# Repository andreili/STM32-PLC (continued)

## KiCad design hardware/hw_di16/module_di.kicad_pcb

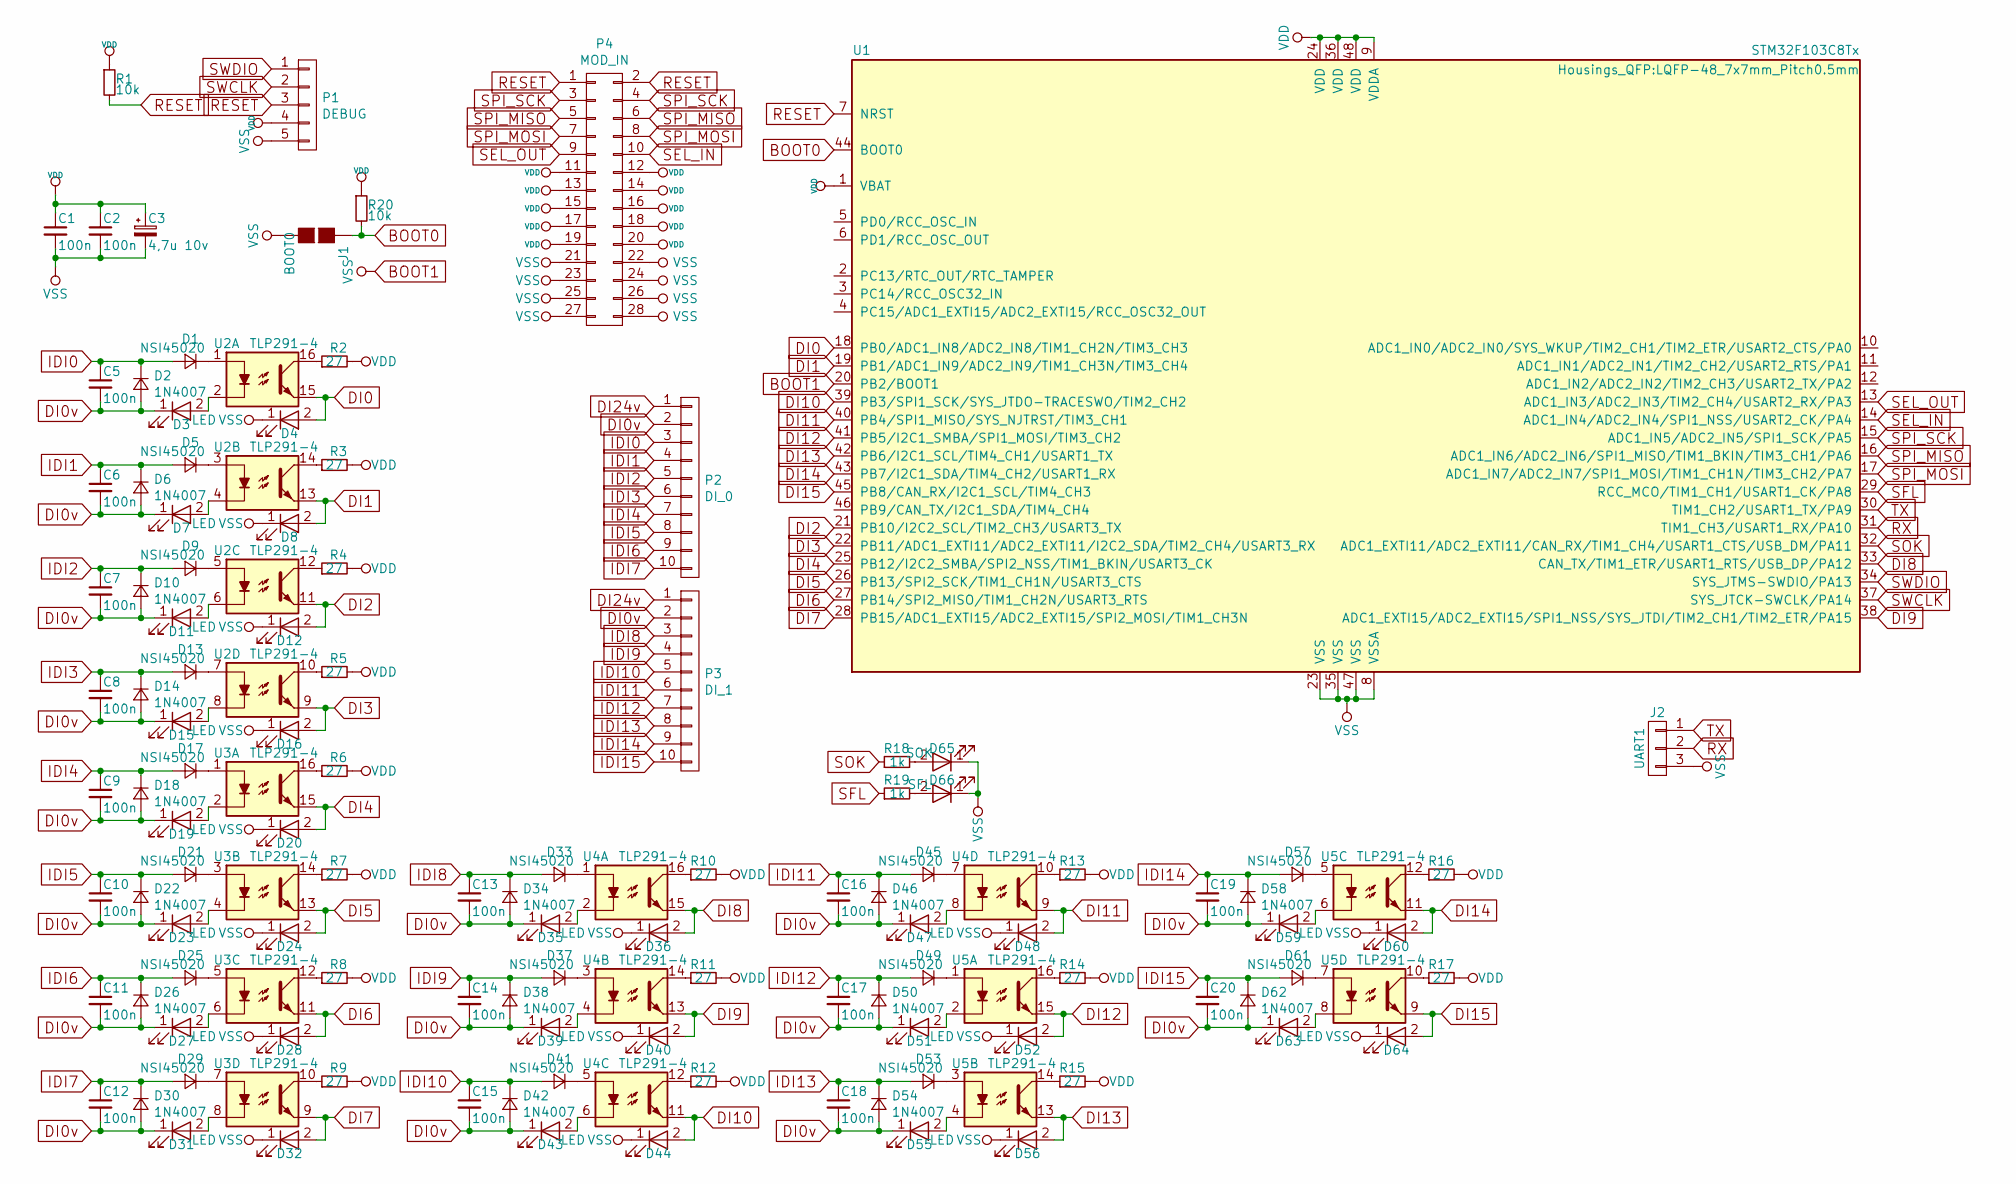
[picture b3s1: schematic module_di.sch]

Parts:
C1, C2, C5, C6, C7, C8, C9, C10, C11, C12, C13, C14, C15, C16, C17, C18, C19, C20: 100n; C_0805
C3: 4,7u 10v; CP_Tantalum_Case-A_EIA-3216-18_Reflow
D1, D5, D9, D13, D17, D21, D25, D29, D33, D37, D41, D45, D49, D53, D57, D61: NSI45020; D_SOD-123
D2, D6, D10, D14, D18, D22, D26, D30, D34, D38, D42, D46, D50, D54, D58, D62: 1N4007; D_SOD-123
D3, D4, D7, D8, D11, D12, D15, D16, D19, D20, D23, D24, D27, D28, D31, D32, D35, D36, D39, D40, D43, D44, D47, D48, D51, D52, D55, D56, D59, D60, D63, D64: LED; LED_0603
D65: SOK; LED_0603
D66: SFL; LED_0603
J1: BOOT0; GS2
J2: UART1; Pin_Header_Straight_1x03_Pitch2.00mm
P1: DEBUG; Pin_Header_Straight_1x05_Pitch2.00mm
P2: DI_0; PhoenixContact_MC-G_10x3.81mm_Angled
P3: DI_1; PhoenixContact_MC-G_10x3.81mm_Angled
P4: MOD_IN; Pin_Header_2.00mm_SMD
R1, R20: 10k; R_0805
R2, R3, R4, R5, R6, R7, R8, R9, R10, R11, R12, R13, R14, R15, R16, R17: 27; R_0805
R18, R19: 1k; R_0805
U1: STM32F103C8Tx; LQFP-48_7x7mm_Pitch0.5mm
U2, U3, U4, U5: TLP291-4; SO-16-N

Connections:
BOOT0: J1.1 (G1), R20.2, U1.44 (BOOT0)
BOOT1: C1.2, C2.2, C3.2, D4.1 (K), D8.1 (K), D12.1 (K), D16.1 (K), D20.1 (K), D24.1 (K), D28.1 (K), D32.1 (K), D36.1 (K), D40.1 (K), D44.1 (K), D48.1 (K), D52.1 (K), D56.1 (K), D60.1 (K), D64.1 (K), D65.1 (K), D66.1 (K), J1.2 (G2), J2.3, P1.5, P4.21, P4.22, P4.23, P4.24, P4.25, P4.26, P4.27, P4.28, U1.8 (VSSA), U1.20 (PB2/BOOT1), U1.23 (VSS), U1.35 (VSS), U1.47 (VSS)
DI0: D4.2 (A), U1.18 (PB0/ADC1_IN8/ADC2_IN8/TIM1_CH2N/TIM3_CH3), U2.15
DI0v: C5.2, C6.2, C7.2, C8.2, C9.2, C10.2, C11.2, C12.2, C13.2, C14.2, C15.2, C16.2, C17.2, C18.2, C19.2, C20.2, D2.2 (A), D3.1 (K), D6.2 (A), D7.1 (K), D10.2 (A), D11.1 (K), D14.2 (A), D15.1 (K), D18.2 (A), D19.1 (K), D22.2 (A), D23.1 (K), D26.2 (A), D27.1 (K), D30.2 (A), D31.1 (K), D34.2 (A), D35.1 (K), D38.2 (A), D39.1 (K), D42.2 (A), D43.1 (K), D46.2 (A), D47.1 (K), D50.2 (A), D51.1 (K), D54.2 (A), D55.1 (K), D58.2 (A), D59.1 (K), D62.2 (A), D63.1 (K), P2.2, P3.2
DI1: D8.2 (A), U1.19 (PB1/ADC1_IN9/ADC2_IN9/TIM1_CH3N/TIM3_CH4), U2.13
DI2: D12.2 (A), U1.21 (PB10/I2C2_SCL/TIM2_CH3/USART3_TX), U2.11
DI3: D16.2 (A), U1.22 (PB11/ADC1_EXTI11/ADC2_EXTI11/I2C2_SDA/T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), U2.9
DI4: D20.2 (A), U1.25 (PB12/I2C2_SMBA/SPI2_NSS/TIM1_BKIN/USART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), U3.15
DI5: D24.2 (A), U1.26 (PB13/SPI2_SCK/TIM1_CH1N/USART3_CTS), U3.13
DI6: D28.2 (A), U1.27 (PB14/SPI2_MISO/TIM1_CH2N/USART3_RTS), U3.11
DI7: D32.2 (A), U1.28 (PB15/ADC1_EXTI15/ADC2_EXTI15/SPI2_MOSI/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), U3.9
DI8: D36.2 (A), U1.33 (CAN_TX/TIM1_ETR/USART1_RTS/USB_DP/PA12), U4.15
DI9: D40.2 (A), U1.38 (ADC1_EXTI15/ADC2_EXTI15/SPI1_NSS/SYS_JT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), U4.13
DI10: D44.2 (A), U1.39 (PB3/SPI1_SCK/SYS_JTDO-TRACESWO/TIM2_CH2), U4.11
DI11: D48.2 (A), U1.40 (PB4/SPI1_MISO/SYS_NJTRST/TIM3_CH1), U4.9
DI12: D52.2 (A), U1.41 (PB5/I2C1_SMBA/SPI1_MOSI/TIM3_CH2), U5.15
DI13: D56.2 (A), U1.42 (PB6/I2C1_SCL/TIM4_CH1/USART1_TX), U5.13
DI14: D60.2 (A), U1.43 (PB7/I2C1_SDA/TIM4_CH2/USART1_RX), U5.11
DI15: D64.2 (A), U1.45 (PB8/CAN_RX/I2C1_SCL/TIM4_CH3), U5.9
DI24v: P2.1, P3.1
IDI0: C5.1, D1.2 (A), D2.1 (K), P2.3
IDI1: C6.1, D5.2 (A), D6.1 (K), P2.4
IDI2: C7.1, D9.2 (A), D10.1 (K), P2.5
IDI3: C8.1, D13.2 (A), D14.1 (K), P2.6
IDI4: C9.1, D17.2 (A), D18.1 (K), P2.7
IDI5: C10.1, D21.2 (A), D22.1 (K), P2.8
IDI6: C11.1, D25.2 (A), D26.1 (K), P2.9
IDI7: C12.1, D29.2 (A), D30.1 (K), P2.10
IDI8: C13.1, D33.2 (A), D34.1 (K), P3.3
IDI9: C14.1, D37.2 (A), D38.1 (K), P3.4
IDI10: C15.1, D41.2 (A), D42.1 (K), P3.5
IDI11: C16.1, D45.2 (A), D46.1 (K), P3.6
IDI12: C17.1, D49.2 (A), D50.1 (K), P3.7
IDI13: C18.1, D53.2 (A), D54.1 (K), P3.8
IDI14: C19.1, D57.2 (A), D58.1 (K), P3.9
IDI15: C20.1, D61.2 (A), D62.1 (K), P3.10
unnamed: D1.1 (K), U2.1
unnamed: D3.2 (A), U2.2
unnamed: D5.1 (K), U2.3
unnamed: D7.2 (A), U2.4
unnamed: D9.1 (K), U2.5
unnamed: D11.2 (A), U2.6
unnamed: D13.1 (K), U2.7
unnamed: D15.2 (A), U2.8
unnamed: D17.1 (K), U3.1
unnamed: D19.2 (A), U3.2
unnamed: D21.1 (K), U3.3
unnamed: D23.2 (A), U3.4
unnamed: D25.1 (K), U3.5
unnamed: D27.2 (A), U3.6
unnamed: D29.1 (K), U3.7
unnamed: D31.2 (A), U3.8
unnamed: D33.1 (K), U4.1
unnamed: D35.2 (A), U4.2
unnamed: D37.1 (K), U4.3
unnamed: D39.2 (A), U4.4
unnamed: D41.1 (K), U4.5
unnamed: D43.2 (A), U4.6
unnamed: D45.1 (K), U4.7
unnamed: D47.2 (A), U4.8
unnamed: D49.1 (K), U5.1
unnamed: D51.2 (A), U5.2
unnamed: D53.1 (K), U5.3
unnamed: D55.2 (A), U5.4
unnamed: D57.1 (K), U5.5
unnamed: D59.2 (A), U5.6
unnamed: D61.1 (K), U5.7
unnamed: D63.2 (A), U5.8
unnamed: D65.2 (A), R18.2
unnamed: D66.2 (A), R19.2
unnamed: R2.1, U2.16
unnamed: R3.1, U2.14
unnamed: R4.1, U2.12
unnamed: R5.1, U2.10
unnamed: R6.1, U3.16
unnamed: R7.1, U3.14
unnamed: R8.1, U3.12
unnamed: R9.1, U3.10
unnamed: R10.1, U4.16
unnamed: R11.1, U4.14
unnamed: R12.1, U4.12
unnamed: R13.1, U4.10
unnamed: R14.1, U5.16
unnamed: R15.1, U5.14
unnamed: R16.1, U5.12
unnamed: R17.1, U5.10
RESET: P1.3, P4.1, P4.2, R1.2, U1.7 (NRST)
RX: J2.2, U1.31 (TIM1_CH3/USART1_RX/PA10)
SEL_IN: P4.10, U1.14 (ADC1_IN4/ADC2_IN4/SPI1_NSS/USART2_CK/PA4)
SEL_OUT: P4.9, U1.13 (ADC1_IN3/ADC2_IN3/TIM2_CH4/USART2_RX/PA3)
SFL: R19.1, U1.29 (RCC_MCO/TIM1_CH1/USART1_CK/PA8)
SOK: R18.1, U1.32 (ADC1_EXTI11/ADC2_EXTI11/CAN_RX/TIM1_CH4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)
SPI_MISO: P4.5, P4.6, U1.16 (ADC1_IN6/ADC2_IN6/SPI1_MISO/TIM1_BKIN/T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)
SPI_MOSI: P4.7, P4.8, U1.17 (ADC1_IN7/ADC2_IN7/SPI1_MOSI/TIM1_CH1N/T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)
SPI_SCK: P4.3, P4.4, U1.15 (ADC1_IN5/ADC2_IN5/SPI1_SCK/PA5)
SWCLK: P1.2, U1.37 (SYS_JTCK-SWCLK/PA14)
SWDIO: P1.1, U1.34 (SYS_JTMS-SWDIO/PA13)
TX: J2.1, U1.30 (TIM1_CH2/USART1_TX/PA9)
VDD: C1.1, C2.1, C3.1, P1.4, P4.11, P4.12, P4.13, P4.14, P4.15, P4.16, P4.17, P4.18, P4.19, P4.20, R1.1, R2.2, R3.2, R4.2, R5.2, R6.2, R7.2, R8.2, R9.2, R10.2, R11.2, R12.2, R13.2, R14.2, R15.2, R16.2, R17.2, R20.1, U1.1 (VBAT), U1.9 (VDDA), U1.24 (VDD), U1.36 (VDD), U1.48 (VDD)

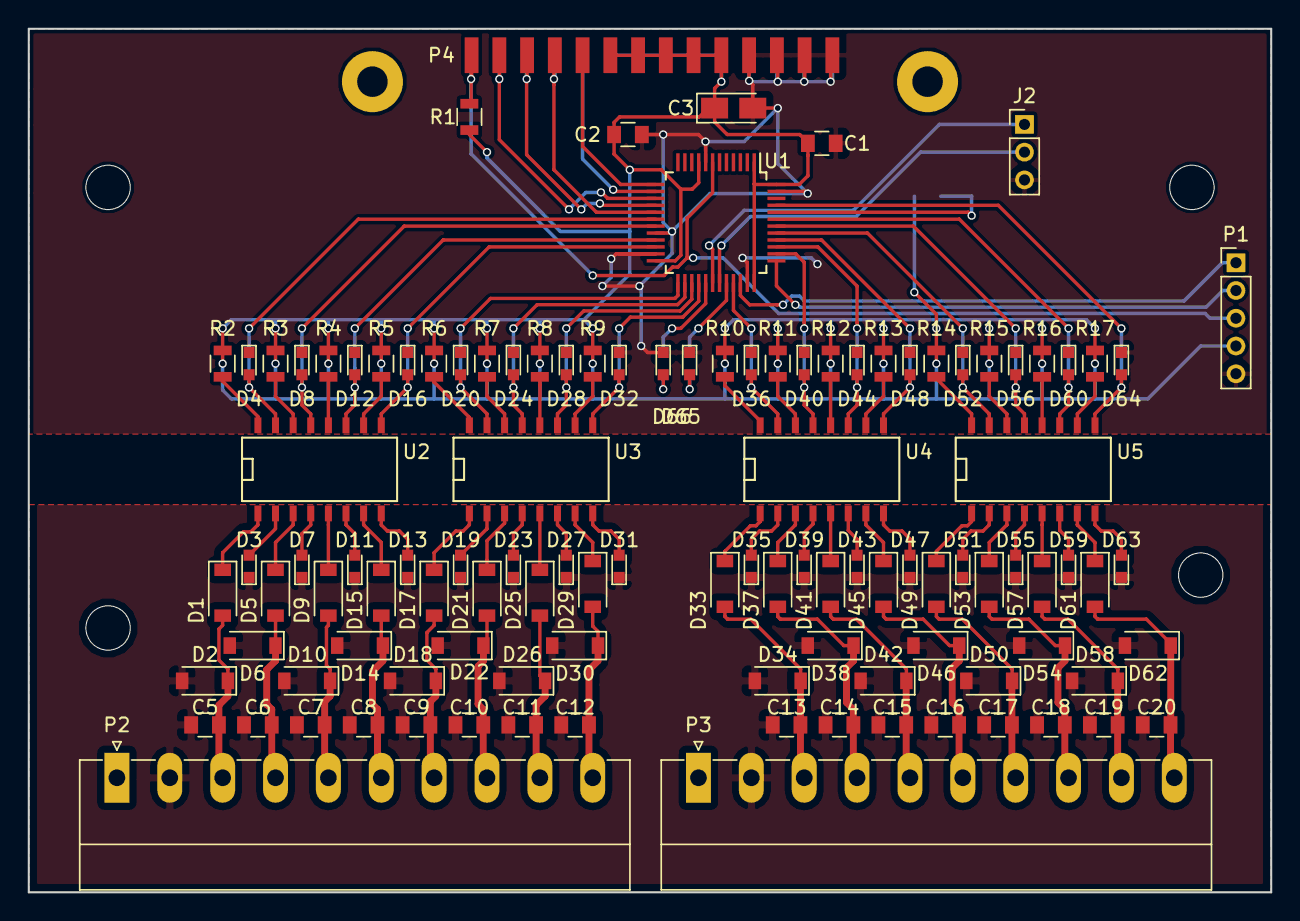
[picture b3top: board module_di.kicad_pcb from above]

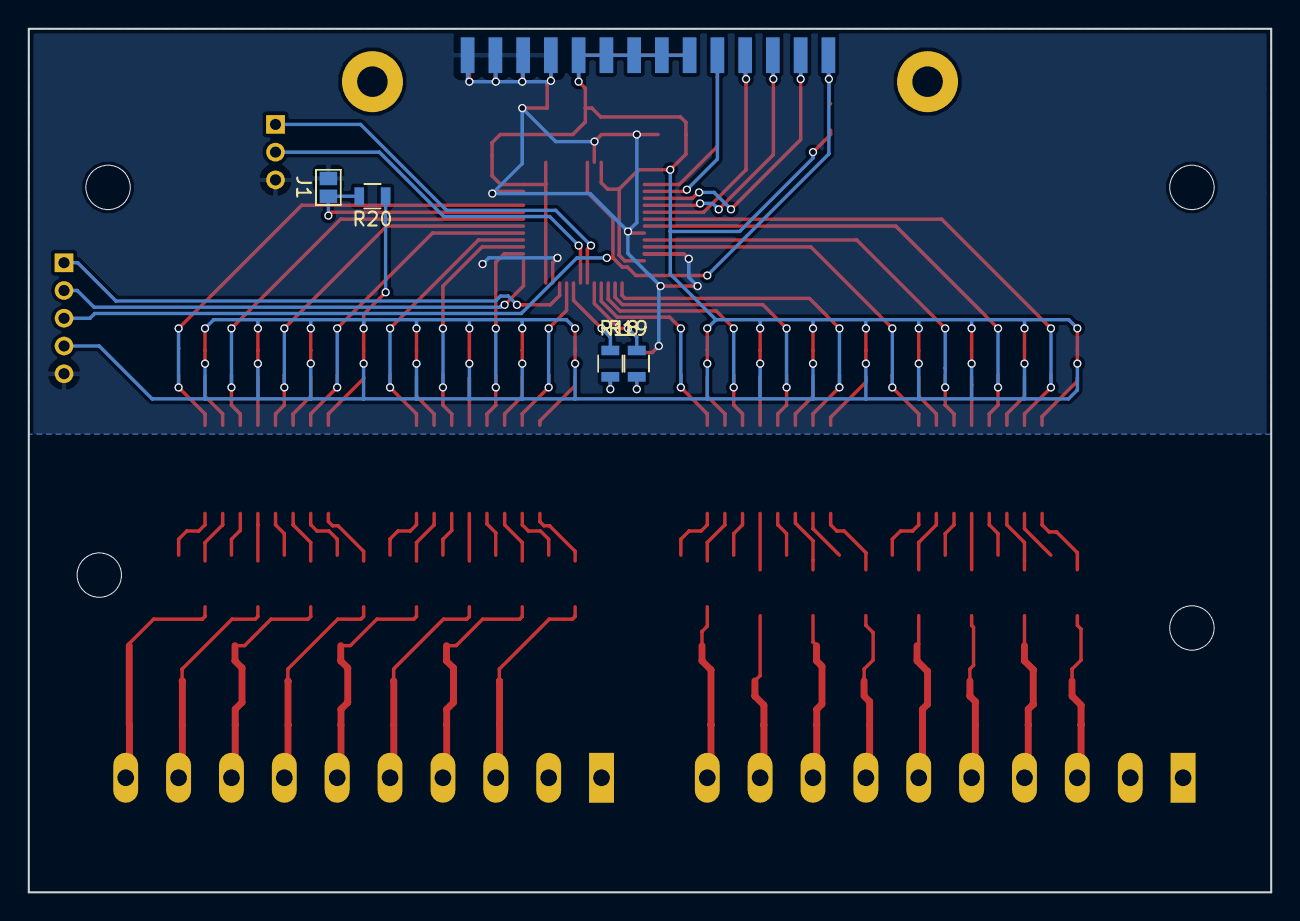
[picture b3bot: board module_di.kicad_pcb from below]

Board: 2 copper layers, 89.5 x 62.2 mm, 116 parts (4 on the bottom side), 99 nets.

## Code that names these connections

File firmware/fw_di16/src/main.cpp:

/* Includes ------------------------------------------------------------------*/
extern "C" {
#include "main.h"
#include "stm32f1xx_hal.h"
}

/* USER CODE BEGIN Includes */
#include "plc_mod.h"
/* USER CODE END Includes */

/* Private variables ---------------------------------------------------------*/
IWDG_HandleTypeDef hiwdg;

SPI_HandleTypeDef hspi1;
DMA_HandleTypeDef hdma_spi1_rx;
DMA_HandleTypeDef hdma_spi1_tx;

/* USER CODE BEGIN PV */
/* Private variables ---------------------------------------------------------*/

/* USER CODE END PV */

/* Private function prototypes -----------------------------------------------*/
void SystemClock_Config(void);
static void MX_GPIO_Init(void);
static void MX_DMA_Init(void);
static void MX_SPI1_Init(void);
static void MX_IWDG_Init(void);

/* USER CODE BEGIN PFP */
/* Private function prototypes -----------------------------------------------*/

/* USER CODE END PFP */

/* USER CODE BEGIN 0 */

/* USER CODE END 0 */

extern "C" {
int main(void)
{

  /* USER CODE BEGIN 1 */

  /* USER CODE END 1 */

  /* MCU Configuration----------------------------------------------------------*/

  /* Reset of all peripherals, Initializes the Flash interface and the Systick. */
  HAL_Init();

  /* USER CODE BEGIN Init */

  /* USER CODE END Init */

  /* Configure the system clock */
  SystemClock_Config();

  /* USER CODE BEGIN SysInit */

  /* USER CODE END SysInit */

  /* Initialize all configured peripherals */
  MX_GPIO_Init();
  MX_DMA_Init();
  MX_SPI1_Init();
  //MX_IWDG_Init();

  /* USER CODE BEGIN 2 */
  HAL_GPIO_WritePin(SEL_IN_GPIO_Port, SEL_IN_Pin, GPIO_PIN_SET);
  //HAL_Delay(300);
  plc_mod.init(&hspi1);
  plc_mod.init_seq();
  /* USER CODE END 2 */

  /* Infinite loop */
  /* USER CODE BEGIN WHILE */
  while (1)
  {
  /* USER CODE END WHILE */

  /* USER CODE BEGIN 3 */

  }
  /* USER CODE END 3 */

}
}

/** System Clock Configuration
*/
void SystemClock_Config(void)
{

  RCC_OscInitTypeDef RCC_OscInitStruct;
  RCC_ClkInitTypeDef RCC_ClkInitStruct;

    /**Initializes the CPU, AHB and APB busses clocks 
    */
  RCC_OscInitStruct.OscillatorType = RCC_OSCILLATORTYPE_HSI|RCC_OSCILLATORTYPE_LSI;
  RCC_OscInitStruct.HSIState = RCC_HSI_ON;
  RCC_OscInitStruct.HSICalibrationValue = 16;
  RCC_OscInitStruct.LSIState = RCC_LSI_ON;
  RCC_OscInitStruct.PLL.PLLState = RCC_PLL_ON;
  RCC_OscInitStruct.PLL.PLLSource = RCC_PLLSOURCE_HSI_DIV2;
  RCC_OscInitStruct.PLL.PLLMUL = RCC_PLL_MUL16;
  if (HAL_RCC_OscConfig(&RCC_OscInitStruct) != HAL_OK)
  {
    Error_Handler();
  }

    /**Initializes the CPU, AHB and APB busses clocks 
    */
  RCC_ClkInitStruct.ClockType = RCC_CLOCKTYPE_HCLK|RCC_CLOCKTYPE_SYSCLK
                              |RCC_CLOCKTYPE_PCLK1|RCC_CLOCKTYPE_PCLK2;
  RCC_ClkInitStruct.SYSCLKSource = RCC_SYSCLKSOURCE_PLLCLK;
  RCC_ClkInitStruct.AHBCLKDivider = RCC_SYSCLK_DIV1;
  RCC_ClkInitStruct.APB1CLKDivider = RCC_HCLK_DIV2;
  RCC_ClkInitStruct.APB2CLKDivider = RCC_HCLK_DIV1;

  if (HAL_RCC_ClockConfig(&RCC_ClkInitStruct, FLASH_LATENCY_2) != HAL_OK)
  {
    Error_Handler();
  }

    /**Configure the Systick interrupt time 
    */
  HAL_SYSTICK_Config(HAL_RCC_GetHCLKFreq()/1000);

    /**Configure the Systick 
    */
  HAL_SYSTICK_CLKSourceConfig(SYSTICK_CLKSOURCE_HCLK);

  /* SysTick_IRQn interrupt configuration */
  HAL_NVIC_SetPriority(SysTick_IRQn, 0, 0);
}

/* IWDG init function */
static void MX_IWDG_Init(void)
{

  hiwdg.Instance = IWDG;
  hiwdg.Init.Prescaler = IWDG_PRESCALER_4;
  hiwdg.Init.Reload = 4095;
  if (HAL_IWDG_Init(&hiwdg) != HAL_OK)
  {
    Error_Handler();
  }

}

/* SPI1 init function */
static void MX_SPI1_Init(void)
{

  hspi1.Instance = SPI1;
  hspi1.Init.Mode = SPI_MODE_SLAVE;
  hspi1.Init.Direction = SPI_DIRECTION_2LINES;
  hspi1.Init.DataSize = SPI_DATASIZE_8BIT;
  hspi1.Init.CLKPolarity = SPI_POLARITY_LOW;
  hspi1.Init.CLKPhase = SPI_PHASE_1EDGE;
  hspi1.Init.NSS = SPI_NSS_HARD_INPUT;
  hspi1.Init.BaudRatePrescaler = SPI_BAUDRATEPRESCALER_128;
  hspi1.Init.FirstBit = SPI_FIRSTBIT_MSB;
  hspi1.Init.TIMode = SPI_TIMODE_DISABLE;
  hspi1.Init.CRCCalculation = SPI_CRCCALCULATION_DISABLE;
  hspi1.Init.CRCPolynomial = 10;
  if (HAL_SPI_Init(&hspi1) != HAL_OK)
  {
    Error_Handler();
  }

}

/** 
  * Enable DMA controller clock
  */
static void MX_DMA_Init(void) 
{
  /* DMA controller clock enable */
  __HAL_RCC_DMA1_CLK_ENABLE();

  /* DMA interrupt init */
  /* DMA1_Channel2_IRQn interrupt configuration */
  HAL_NVIC_SetPriority(DMA1_Channel2_IRQn, 0, 0);
  HAL_NVIC_EnableIRQ(DMA1_Channel2_IRQn);
  /* DMA1_Channel3_IRQn interrupt configuration */
  HAL_NVIC_SetPriority(DMA1_Channel3_IRQn, 0, 0);
  HAL_NVIC_EnableIRQ(DMA1_Channel3_IRQn);

}

/** Configure pins as 
        * Analog 
        * Input 
        * Output
        * EVENT_OUT
        * EXTI
        * Free pins are configured automatically as Analog (this feature is enabled through 
        * the Code Generation settings)
*/
static void MX_GPIO_Init(void)
{

  GPIO_InitTypeDef GPIO_InitStruct;

  /* GPIO Ports Clock Enable */
  __HAL_RCC_GPIOC_CLK_ENABLE();
  __HAL_RCC_GPIOD_CLK_ENABLE();
  __HAL_RCC_GPIOA_CLK_ENABLE();
  __HAL_RCC_GPIOB_CLK_ENABLE();

  /*Configure GPIO pin Output Level */
  HAL_GPIO_WritePin(SEL_OUT_GPIO_Port, SEL_OUT_Pin, GPIO_PIN_SET);

  /*Configure GPIO pins : DI0_Pin DI1_Pin DI2_Pin */
  GPIO_InitStruct.Pin = DI0_Pin|DI1_Pin|DI2_Pin;
  GPIO_InitStruct.Mode = GPIO_MODE_INPUT;
  GPIO_InitStruct.Pull = GPIO_PULLUP;
  HAL_GPIO_Init(GPIOC, &GPIO_InitStruct);

  /*Configure GPIO pin : SEL_IN_Pin */
  GPIO_InitStruct.Pin = SEL_IN_Pin;
  GPIO_InitStruct.Mode = GPIO_MODE_INPUT;
  GPIO_InitStruct.Pull = GPIO_PULLUP;
  HAL_GPIO_Init(SEL_IN_GPIO_Port, &GPIO_InitStruct);

  /*Configure GPIO pin : SEL_OUT_Pin */
  GPIO_InitStruct.Pin = SEL_OUT_Pin;
  GPIO_InitStruct.Mode = GPIO_MODE_OUTPUT_PP;
  GPIO_InitStruct.Speed = GPIO_SPEED_FREQ_LOW;
  HAL_GPIO_Init(SEL_OUT_GPIO_Port, &GPIO_InitStruct);

  /*Configure GPIO pin : DI3_Pin */
  GPIO_InitStruct.Pin = DI3_Pin;
  GPIO_InitStruct.Mode = GPIO_MODE_INPUT;
  GPIO_InitStruct.Pull = GPIO_NOPULL;
  HAL_GPIO_Init(DI3_GPIO_Port, &GPIO_InitStruct);

  /*Configure GPIO pins : DI4_Pin DI5_Pin DI6_Pin DI7_Pin 
                           DI12_Pin DI13_Pin DI14_Pin DI15_Pin */
  GPIO_InitStruct.Pin = DI4_Pin|DI5_Pin|DI6_Pin|DI7_Pin 
                          |DI12_Pin|DI13_Pin|DI14_Pin|DI15_Pin;
  GPIO_InitStruct.Mode = GPIO_MODE_INPUT;
  GPIO_InitStruct.Pull = GPIO_PULLUP;
  HAL_GPIO_Init(GPIOA, &GPIO_InitStruct);

  /*Configure GPIO pins : PB0 PB1 PB2 PB10 
                           PB11 PB3 PB4 PB5 
                           PB6 PB7 PB8 PB9 */
  GPIO_InitStruct.Pin = GPIO_PIN_0|GPIO_PIN_1|GPIO_PIN_2|GPIO_PIN_10 
                          |GPIO_PIN_11|GPIO_PIN_3|GPIO_PIN_4|GPIO_PIN_5 
                          |GPIO_PIN_6|GPIO_PIN_7|GPIO_PIN_8|GPIO_PIN_9;
  GPIO_InitStruct.Mode = GPIO_MODE_ANALOG;
  HAL_GPIO_Init(GPIOB, &GPIO_InitStruct);

  /*Configure GPIO pins : DI8_Pin DI9_Pin DI10_Pin DI11_Pin */
  GPIO_InitStruct.Pin = DI8_Pin|DI9_Pin|DI10_Pin|DI11_Pin;
  GPIO_InitStruct.Mode = GPIO_MODE_INPUT;
  GPIO_InitStruct.Pull = GPIO_PULLUP;
  HAL_GPIO_Init(GPIOB, &GPIO_InitStruct);

  /*Configure GPIO pins : PA12 PA15 */
  GPIO_InitStruct.Pin = GPIO_PIN_12|GPIO_PIN_15;
  GPIO_InitStruct.Mode = GPIO_MODE_ANALOG;
  HAL_GPIO_Init(GPIOA, &GPIO_InitStruct);

  /*Configure peripheral I/O remapping */
  __HAL_AFIO_REMAP_PD01_ENABLE();

}

/* USER CODE BEGIN 4 */

/* USER CODE END 4 */

/**
  * @brief  This function is executed in case of error occurrence.
  * @param  None
  * @retval None
  */
extern "C" {
void Error_Handler()
{
  /* USER CODE BEGIN Error_Handler_Debug */
  /* User can add his own implementation to report the HAL error return state */
  while(1) 
  {
  }
  /* USER CODE END Error_Handler_Debug */ 
}
}

#ifdef USE_FULL_ASSERT

/**
   * @brief Reports the name of the source file and the source line number
   * where the assert_param error has occurred.
   * @param file: pointer to the source file name
   * @param line: assert_param error line source number
   * @retval None
   */
void assert_failed(uint8_t* file, uint32_t line)
{
  /* USER CODE BEGIN 6 */
  /* User can add his own implementation to report the file name and line number,
    ex: printf("Wrong parameters value: file %s on line %d\r\n", file, line) */
  /* USER CODE END 6 */

}

#endif

/**
  * @}
  */ 

/**
  * @}
*/ 

/************************ (C) COPYRIGHT STMicroelectronics *****END OF FILE****/

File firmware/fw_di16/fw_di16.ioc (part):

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Mcu.Name=STM32F103C(8-B)Tx
Mcu.Package=LQFP48
Mcu.UserName=STM32F103C8Tx
PA13.Mode=Serial_Wire
PA13.Signal=SYS_JTMS-SWDIO
PA14.Mode=Serial_Wire
PA14.Signal=SYS_JTCK-SWCLK
PA5.Mode=Full_Duplex_Slave
PA5.Signal=SPI1_SCK
PA6.Mode=Full_Duplex_Slave
PA6.Signal=SPI1_MISO
PA7.Mode=Full_Duplex_Slave
PA7.Signal=SPI1_MOSI
PD0-OSC_IN.Signal=GPIO_Input
PD1-OSC_OUT.Signal=GPIO_Output
RCC.SYSCLKFreq_VALUE=64000000
RCC.SYSCLKSource=RCC_SYSCLKSOURCE_PLLCLK
board=fw_di16

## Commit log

2017-07-19 Inital commit
2017-07-19 Fix .gitignore rules
2017-07-19 Исправлено имя класса STM32_SYSTICK
2017-07-19 Исправлены имена методов в STM32_RCC
2017-07-19 Реализован базовый функционал STM32_PWR (только из HAL_PWR_EX)
2017-07-20 Дописан класс STM32_RCC
2017-07-20 Исправлен класс STM32_FLASH
2017-07-20 Завершен класс STM32_PWR
2017-07-20 Завершен класс STM32_SYSTICK
2017-07-21 Исправлена оптимизация переменной таймера
2017-07-21 Добавлена реализация xprintf
2017-07-21 Добавлена инициализация SDRAM
2017-07-21 Исправлена частота обновления памяти и добавлено тестирование памяти
2017-07-21 Добавлен класс для управления состоянием PLC
2017-07-21 Добавлено состояние "инициализация" и исправлена индикация режимов работы PLC.
2017-07-22 Добавлена инициализация стека
2017-07-23 Включение кэширования и буфера сделаны опциональными
2017-07-23 Добавлен класс STM32_NVIC
2017-07-23 Инициализация UART разбита на 2 этапа
2017-07-23 Исправлена очередность инициализации
2017-07-23 Все требуевые включения файлов вынесены в отдельный заголовочный файл
2017-07-23 Вывод текста перенесен в main.cpp
2017-07-23 Убрана очистка памяти при сбросе контроллера
2017-07-23 Оптимизирован код класса STM32_UART
2017-07-24 Оптимизировано управление индикацией состояния PLC
2017-07-24 Обновлен код класса STM32_UART
2017-07-24 Обновлен код инициализации и обработки прерываний
2017-07-24 Исправлена опечатка в инициализации GPIO
2017-07-24 исправлена инициализация и работа UART
2017-07-24 Добавлена инициализация векторов прерываний для переферии
2017-07-24 Вывод текстовых сообщений вынесен в класс PLC_CONTROL
2017-07-25 Обновлена инициализация SDRAM
2017-07-26 Время выполнения команд SDRAM вынесено в константу
2017-07-26 Обновлен код инициализации SysTick
2017-07-26 Завершена отладка инициализации памяти
2017-07-26 Исправлено зависание при отправке данных в UART
2017-07-26 Добавлена инициализация FPU
2017-07-26 Оптимизация системных функций по скорости
2017-07-26 Добавлен тест скорости памяти
2017-07-26 Исправлена опечатка
2017-07-26 Обновлен вывод информации
2017-07-26 Добавлена FPU-libc для линковки
2017-07-26 Увеличена тактовая частота
2017-07-26 Убраны "волшебные числа"
2017-07-28 Добавлена начальная поддержка FatFS
2017-08-01 Добавлен черновой вариант класса STM32_SPI
2017-08-03 Бибилотеки перенесены в общий каталог проекта. Добавлена поддрежка STM32F1xx
2017-08-03 Добавлена инициализация модулей PLC
2017-08-03 Добавлен код для STM32F1xx
2017-08-03 Добавлен проект модуля DI
2017-08-03 Исправлена инициализация RCC
2017-08-03 Исправлен расчет стека и расположение GOT для STM32F1xx
2017-08-03 Добавлена начальная поддержка модулей в CPU
2017-08-03 Добавлены общие файлы для прошивок модулей
2017-08-03 Добавлен базовый проект модуля DI16
2017-08-03 Добавлена последовательность инициализации модуля
2017-08-03 Перемещены оставшиеся общие файлы
2017-08-04 Шина EXT-MOD переведена на аппаратный сигнал NSS
2017-08-04 MOD: Добавлена обработка входов/выходов шины
2017-08-06 Оптимизация инициализации модуля по скорости
2017-08-07 Добавлена черновая схема модуля DI16
2017-08-08 Обновлена схема модуля DI16
2017-08-08 Обработка NSS модуля переведена в аппаратный режим
2017-08-08 Добавлена схема модуля CPU
2017-08-09 Обновлена схема CPU
2017-08-09 Обновлена плата CPU
2017-08-11 Обновлены схема и плата CPU.
    Добавлены переключатель START/STOP, кнопки DUMP и RESTORE.
2017-08-11 Добавлен список TODO
2017-08-13 Обновлена плата CPU.
    Завершена предварительная трассировка
2017-08-13 Обновлена плата CPU.
    Исправлен шелк для батарейки
2017-08-14 Обновлена плата CPU.
2017-08-16 Обновлена плата CPU.
    Добавлены размеры
2017-08-16 Обновлена плата DI16.
    Завершена предварительная разводка.
2017-08-16 Добавлена кросс-плата для соединения модулей.
2017-08-16 Добавлена плата для соединения модуля с кросс-модулем
2017-08-16 Добавлена предварительная версия платы модуля DO16.
2017-08-18 Обновлена плата модуля DI16.
    Добавлены статусные светодиоды.
2017-08-18 Обновлена плата модуля DO16.
    Завершена предварительная трассировка.
2017-08-18 Обновлена кросс-плата для модулей.
2017-08-18 Обновлена шелкография на платах.
2017-08-22 Обновлена плата кросс-модуля.
    Добавлена буферизация шины.
2017-08-22 Обновлены платы модулей - приведены к единому виду.
2017-08-23 Обновлены платы модулей.
    Добавлен разъем для работы с аппаратным загрузчиком.
2017-09-01 Добавлен отладочный вывод монтирования SD-карты
2017-09-01 Обновлены платы модулей
2017-09-01 Исправлено расположение файлов проекта
2017-09-20 Firmware: Убраны блоки кода для STM32F1xx
2017-09-20 Firmware: Удалены дубликаты общих файлов.
2017-09-20 Firmware: Исправлены опечатки в коде.
2017-09-20 Обновлено до последней версии платы.
2017-09-21 Обновлен код обработки состояний PLC
2017-09-21 Обновлена работа с SD-картой
2017-09-21 Исправлена ошибка инициализации SD-карты.
2017-09-22 STM32_SD: Добавлены недостающие функции
2017-09-22 Добавлена обработка записи на SD карту
2017-09-22 Исправлено назначение вывода CARD_DETECT
2017-09-22 Перемещено тело функции Error_Handler
2017-09-22 Добавлен черновой класс STM32_RTC
2017-09-23 Исправлена инициализация RTC
2017-09-23 Исправлена инициализация тактирования
2017-09-23 Процедуры инициализации и главный цикл перенесены в класс PLC_CONTROL
2017-09-23 Оптимизация инициализации
2017-09-23 Исправлена заморозка регистров RTC при чтении из RTC->SSR
2017-09-23 Обновлена работа со статусными полями ПЛК
2017-09-23 Добавлен класс PLC_STATE
2017-09-23 Добавлен расчет времени цикла
2017-09-24 Оптимизация кода RTC
2017-09-24 Время цикла рассчитывается как среднее между 10 циклами
2017-09-24 Добавлен вывод времени цикла
2017-10-27 Адаптация прошивки для 2-х платформ
2017-10-27 Добавлена обработка программы STL.
2017-10-29 Исправлены загрузка и выполнение прошивки.
2017-10-29 Начало реализации компилятора ST(L) .
2017-10-29 STLC: Первичная реализация парсинга.
2017-10-29 STLC: Добавлены тестовые листинги.
2017-10-30 STLC: Оптимизация кода.
2017-10-30 STLC: Реализован базовый парсинг STL.
2017-12-08 Добавлен базовый runtime, требуется проверка на устройстве.
2017-12-26 HW: Обновлена схема CPU.
2017-12-27 HW: Обновлена схема CPU
2017-12-27 Runtime: Адаптация под SoftPLC (включая FPGA DE1-SoC).
2017-12-29 Runtime: Обновлена обработка модулей на шине.
2017-12-29 Runtime: Исправлена обработка ошибок загрузки.
2017-12-29 Runtime: Добавлена обработка ошибок модулей.
2018-01-03 Runtime: Переведено на конечный автомат состояний PLC.
2018-01-03 Runtime: Убрано динамическое выделение памяти под объекты.
2018-01-03 Runtime: Добавлены заготовки блоков OB.
2018-01-03 Runtime: Добавлены зарезервированные переходы между состояниями PLC.
2018-01-03 Runtime: Обработка ошибки выполнения программы вынесена в OB84.
2018-01-03 Runtime: Исправлено подключение заголовков для FPGA.
2018-01-03 Runtime: Загрузка сведений о модулях перенесена в класс PLCBus.
2018-01-03 Runtime: Добавлено чтение Profibus и Profinet аресов модулей.
2018-01-04 Runtime: Унификация интерфейсов обращения к данным.
2018-01-05 Runtime: Обработка данных в памяти сведена к единому интерфейсу.
2018-01-05 Runtime: В примере прошивки реализован алгоритм с самоподхватом.
2018-01-05 Runtime: Исправлен пропуск чтения/записи входов/выходов.
2018-01-05 Runtime: Реализовано вычисление времени цикла.
2018-01-05 Runtime: Различные процессы разнесены по потокам со своим минимальным временем цикла.
